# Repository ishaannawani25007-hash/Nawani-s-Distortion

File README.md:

Hi everyone :3 i am Ishaan Nawani from India, i am 16 years old. I wanted to say that the experience the learning and the designing in the process of creating this project was very amazing , i managed to build this in really less amount of time, I had to learn PCB designing , how to make CAD files and etc. but the experience and what i learned in the way was priceless and i loved doing this project and i never imagined in a million years that i would be able to pull this off <3.

.

.

.

.

Project Description – Transistor Guitar Distortion Pedal

This project is a small distortion pedal made with transistors.
It takes the sound from an electric guitar and changes it to make a distorted tone that works well with rock and experimental music. The pedal uses a high-gain NPN transistor to boost the signal and diodes to clip the waveform, which creates the distortion effect. It runs on a 9V DC power supply and has a 3PDT footswitch for switching between bypass and distortion mode. There's also an LED light that shows if the pedal is on.

The project includes a custom-designed PCB made in KiCad, wires for the footswitch, audio jacks, and power input, and a 3D layout for the enclosure.

It is really simple to use it too:

To use the pedal, connect your electric guitar to the input jack and plug the output jack into an amplifier.
Then, connect a 9V DC power supply to the pedal.

When you press the 3PDT footswitch, it turns the pedal on or off.
When it's on, the LED lights up and the signal goes through the distortion circuit, changing the sound to a distorted tone. When it's off, the signal goes straight from input to output without any change.

Wondering why i made this project?
I made this project to learn about analog audio electronics and guitar effects.
The main aim was to understand how transistor amplification, biasing, and diode clipping affect the guitar signal to create distortion.

Building the pedal also helped me learn how to design PCBs in KiCad, wire hardware, and layout enclosures.
Instead of just copying an existing pedal, I created my own design and layout to better understand the whole process of building a pedal from a circuit diagram to the final product.

*_Images:_*

PCB Layout:
[FILE](https://github.com/ishaannawani25007-hash/Nawani-s-Distortion/tree/main/PCB)

The hardest part specially for me was to design the PCB as i am not an absolute professional at this although i did manage to make this from the schematic and was fun.

CAD Enclosure
[FILE](https://github.com/ishaannawani25007-hash/Nawani-s-Distortion/blob/main/CAD/EnclosureBodyLedVertical.STL)

[FILE](https://github.com/ishaannawani25007-hash/Nawani-s-Distortion/blob/main/CAD/BottomPart.STL)

_Wiring_

There is no fancy wiring i have made the pcb in such a way such that the layout of the pcb mainly the terminals are easy to understand and follow the PedalPCB website's wiring diagram, it has made my work a lot easier and the diagram also shows how to easily wire the pedal.

The wiring labels on the board indicate the following:

InG - Intended for input jack ground

In - Input Jack Signal

SW - Switch connection to footswitch

SwG - Ground connection to footswitch

O - Output Jack Signal

OG - Intended for output jack ground

Gnd - Intended for power jack ground

9v - Positive 9v power

Note: The pedal wiring works the same as most 'PedalPCB' pedals ,I have designed the circuit with that in mind. You can use this  [this build documentation](https://docs.pedalpcb.com/project/Amentum.pdf) build documentation as a wiring reference.

List Of Material 

Theese materials are MOSTLY from robu although some parts if any that wont be on the website are updated below and links to each and every component is also given.

[Material List](https://github.com/ishaannawani25007-hash/Nawani-s-Distortion/blob/main/BOM.csv)

RESISTORS (1/4 watt)

| QTY | VALUE |

| 1 | [390](https://robu.in/product/mf25-390r-multicomp-pro-through-hole-resistor-390-ohm-mf25-series-250-mw-±-1-axial-leaded-250-v/) ohm |

| 1 | [4K7](https://robu.in/product/mf25-4k7-multicomp-pro-through-hole-resistor-4-7-kohm-250-mw-±-1-axial-leaded-250-v/) ohm |

| 1 | [10K](https://robu.in/product/mf25-10k-multicomp-pro-through-hole-resistor-10-kohm-250-mw-±-1-axial-leaded-250-v/) ohm |

| 1 | [43K](https://robu.in/product/mf25-43k-multicomp-pro-through-hole-resistor-43-kohm-mf25-series-250-mw-±-1-axial-leaded-250-v/) ohm |

| 1 | [430K](https://robu.in/product/mf25-430k-multicomp-pro-through-hole-resistor-430-kohm-mf25-series-250-mw-±-1-axial-leaded-250-v/) ohm |

CAPACITORS

| QTY | VALUE |

| 2 | [0.1 UF](https://robu.in/product/100nf-50v-disc-capacitor/) (100nF) |

TRANSISTORS(currently not available on Robu)

| QTY | Part # |

| 1 | [2N5088](https://www.amazon.in/2N5088-Transistor-NPN/dp/B08YFF1JN7) |

DIODES

| QTY | Part # |

| 1 | [1N5817](https://robu.in/product/1n5817-t-diodes-incorporated-20v-750mv3a-1a-do-41-schottky-diodes-rohs/) |

| 1 | [5mm LED](https://robu.in/product/tj-l5fytghrmfcsflc2r-a5-togialed-20ma-foggy-red-lens-20℃80℃-red-45-5mm-round-lamp-head-plugind5mm-led-indication-discrete-rohs/) (color of choice) |

POTENTIOMETERS

| QTY | VALUE |

| 1 | [A100K](https://robu.in/product/p160knp-0qc20a100k-tt-electronics-bi-technologies/) | Note: B100K for linear taper works fine. Use 16mm right angle PCB mount if using 1590a drill template.

SWITCHES

1 | [3DPDT footswitch](https://robu.in/product/pbs-24-302-latching-push-button-switch-9pin/)

JACKS

2 | [1/4" Mono Audio Jack](https://robu.in/product/1-month-warranty-179/)

1 | 9 volt power from [PSU:](https://robu.in/product/dc-jack-022/) or [Battery:](https://robu.in/product/9v-battery-snap-connector-dc-jackbattery-connector-cap/) (center negative) Note: No space for battery in 1590a enclosure

============================================================================================

ALL THE DESIGNING AND MODELLING WERE DONE ON

  . [Kicad](https://www.kicad.org)
          
  . [Blender](https://www.blender.org)

. PCB From

  . [JlcPcb](https://jlcpcb.com)

.  Components From

  . [Robu](https://robu.in) & [Amazon](https://www.amazon.in)

===========================================================================================

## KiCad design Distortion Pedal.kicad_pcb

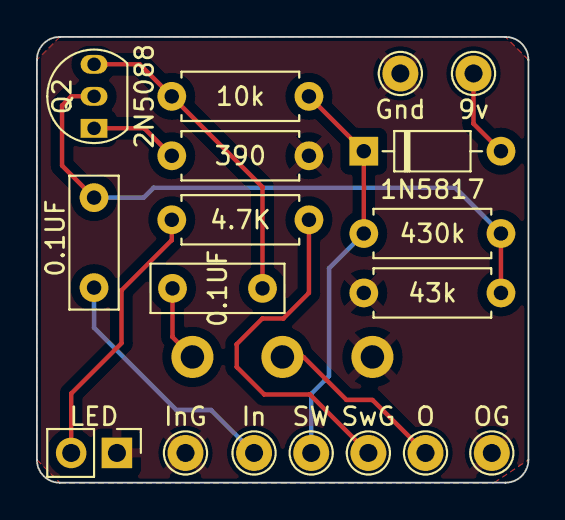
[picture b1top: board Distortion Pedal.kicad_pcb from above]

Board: 2 copper layers, 27.3 x 24.8 mm, 19 parts (0 on the bottom side), 11 nets.

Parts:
9v: TestPoint_THTPad_D2.0mm_Drill1.0mm
C1, C2: 0.1UF; C_Rect_L7.2mm_W2.5mm_P5.00mm_FKS2_FKP2_MKS2_MKP2
D1: 1N5817; D_DO-35_SOD27_P7.62mm_Horizontal
Gnd: TestPoint_THTPad_D2.0mm_Drill1.0mm
In: TestPoint_THTPad_D2.0mm_Drill1.0mm
InG: TestPoint_THTPad_D2.0mm_Drill1.0mm
LED: PinHeader_1x02_P2.54mm_Vertical
O: TestPoint_THTPad_D2.0mm_Drill1.0mm
OG: TestPoint_THTPad_D2.0mm_Drill1.0mm
POT1: 100K; Potentiometer_Omeg_PC16BU_Vertical
Q2: 2N5088; TO-92_Inline
R1: 430k; R_Axial_DIN0207_L6.3mm_D2.5mm_P7.62mm_Horizontal
R2: 43k; R_Axial_DIN0207_L6.3mm_D2.5mm_P7.62mm_Horizontal
R3: 10k; R_Axial_DIN0207_L6.3mm_D2.5mm_P7.62mm_Horizontal
R4: 390; R_Axial_DIN0207_L6.3mm_D2.5mm_P7.62mm_Horizontal
R5: 4.7K; R_Axial_DIN0207_L6.3mm_D2.5mm_P7.62mm_Horizontal
SW: TestPoint_THTPad_D2.0mm_Drill1.0mm
SwG: TestPoint_THTPad_D2.0mm_Drill1.0mm

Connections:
GND: Gnd.1, InG.1, LED.1 (K), OG.1, POT1.1, R2.1, R4.1
unnamed: 9v.1, D1.2 (A)
unnamed: C2.2, POT1.3
unnamed: D1.1 (K), R1.2, R3.2, SW.1
unnamed: C1.1, In.1
unnamed: LED.2 (A), R5.1
unnamed: O.1, POT1.2
unnamed: C1.2, Q2.2 (B), R1.1, R2.2
unnamed: C2.1, Q2.3 (C), R3.1
unnamed: Q2.1 (E), R4.2
unnamed: R5.2, SwG.1

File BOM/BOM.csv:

RESISTORS (1/4 watt)
| QTY | VALUE |
| 1 | 390 ohm |https://robu.in/product/mf25-390r-multicomp-pro-through-hole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
| 1 | 4K7 |https://robu.in/product/mf25-4k7-multicomp-pro-through-hole-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
| 1 | 10K |https://robu.in/product/mf25-10k-multicomp-pro-through-hole-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
| 1 | 43K |https://robu.in/product/mf25-43k-multicomp-pro-through-hole-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
| 1 | 430K |https://robu.in/product/mf25-430k-multicomp-pro-through-hole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


CAPACITORS
| QTY | VALUE |
| 2 | 0.1 UF (100nF) |https://robu.in/product/100nf-50v-disc-capacitor/


TRANSISTORS
| QTY | Part # |
| 1 | 2N5088 | https://robu.in/product/2n3904-tarange200-300-jcet-40v-625mw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


DIODES
| QTY | Part # |
| 1 | 1N5817 |https://robu.in/product/1n5817-t-diodes-incorporated-20v-750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
| 1 | 5mm LED (color of choice) | https://robu.in/product/tj-l5fytghrmfcsflc2r-a5-togialed-20m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

POTENTIOMETERS
| QTY | VALUE |
| 1 | A100K | https://robu.in/product/p160knp-0qc20a100k-tt-electronics-bi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

SWITCHES
1 | 3DPDT footswitch https://robu.in/product/pbs-24-302-latching-push-button-swit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

JACKS
2 | 1/4" Mono Audio Jack https://robu.in/product/1-month-warranty-179/
1 | 9 volt power jack (center negative) https://robu.in/product/dc-jack-022/

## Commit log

2026-02-27 CAD Enclosure
2026-02-27 ImgCad
2026-03-12 Materials
2026-03-12 Images
2026-03-12 Wiring
2026-03-12 Enclosure
2026-03-12 Cost
